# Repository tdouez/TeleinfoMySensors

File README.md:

# TeleinfoMySensors v2.1.0

Interface Téléinfo pour compteur Linky avec MySensors - version compatible mode standard et historique

Projet utilisant un Arduino Pro micro et un module NRF24L01

- Hardware disponible sur https://www.openhardware.io/view/744/MySensors-Linky
- Boîtier disponible sur https://www.thingiverse.com/thing:3985437
- Description disponible sur http://fumeebleue.fr

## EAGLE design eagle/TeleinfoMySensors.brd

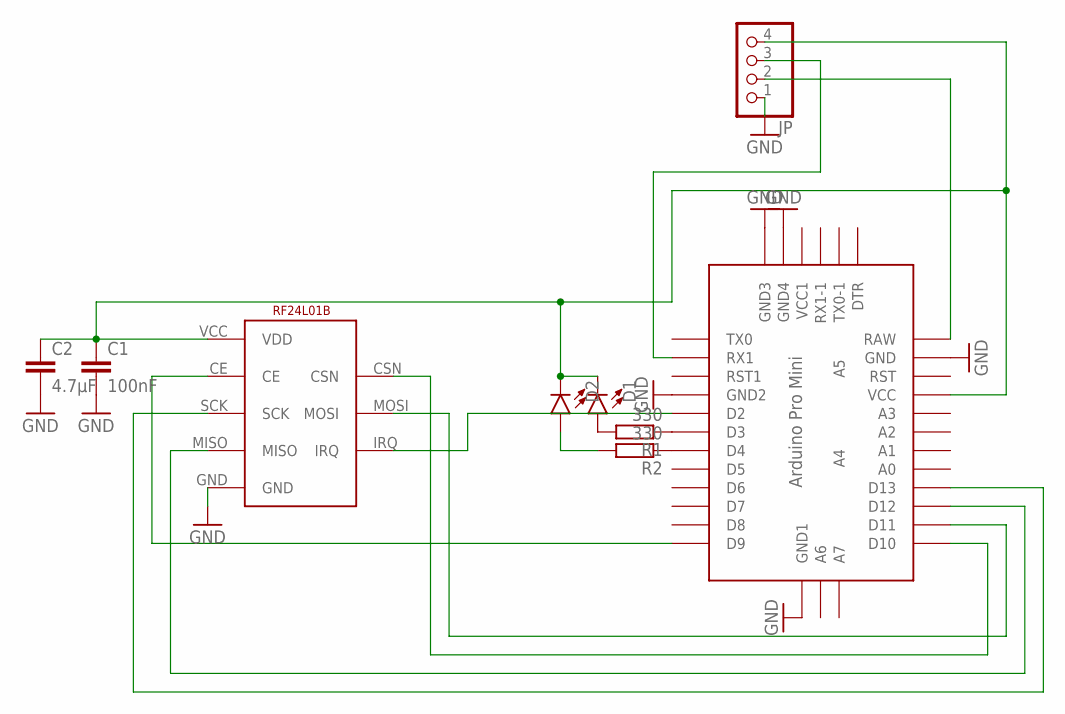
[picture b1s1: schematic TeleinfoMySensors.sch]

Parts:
C1: 100nF; C1206
C2: 4.7µF; C1210
D1, D2: LED1206; LED-1206
JP: PINHD-1X4; 1X04
NRF: NRF24L01BLACK; 24L01BLACK
R1, R2: 330; M1206
U$1: ABK-PRO-MINI

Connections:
GND: C1.2, C2.2, JP.1, NRF.GND, U$1.GND, U$1.GND1 (GND2), U$1.GND2 (GND3), U$1.GND3 (GND4), U$1.GND4 (GND1)
unnamed: NRF.CE, U$1.D9
unnamed: D1.A, R1.2
unnamed: NRF.SCK, U$1.D13
unnamed: R1.1, U$1.D3
unnamed: NRF.MOSI, U$1.D11
unnamed: NRF.MISO, U$1.D12
unnamed: JP.2, U$1.RAW
unnamed: R2.1, U$1.D4
unnamed: D2.A, R2.2
unnamed: JP.3, U$1.RX1
unnamed: C1.1, C2.1, D1.C, D2.C, JP.4, NRF.VCC (VDD), U$1.VCC
unnamed: NRF.IRQ, U$1.D2
unnamed: NRF.CSN, U$1.D10

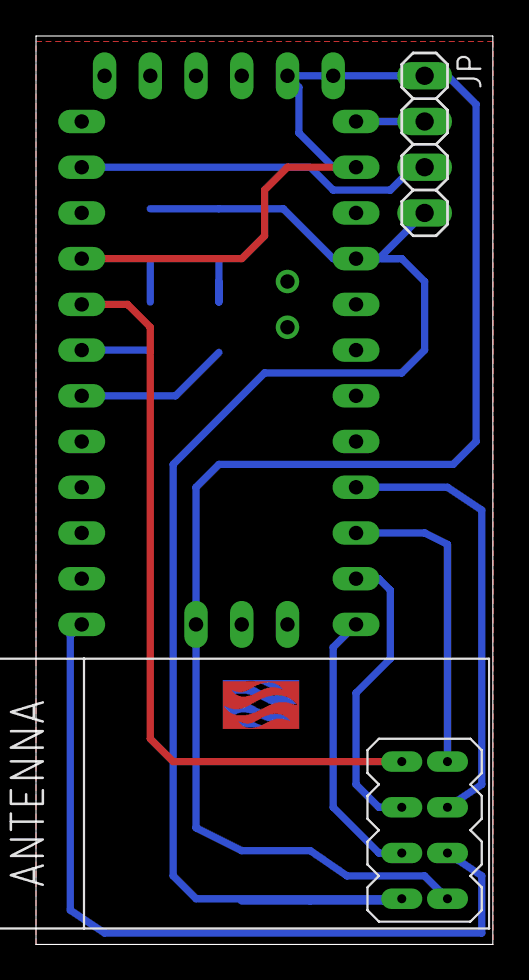
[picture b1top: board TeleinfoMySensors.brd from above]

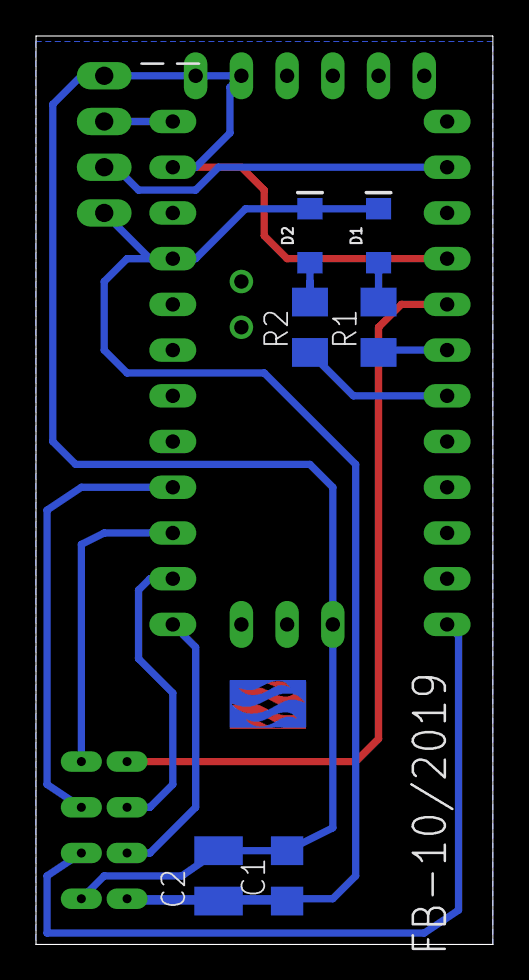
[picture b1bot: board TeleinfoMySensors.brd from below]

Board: 2 copper layers, 25.4 x 50.5 mm, 11 parts (7 on the bottom side), 14 nets.

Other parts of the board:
U$3, U$4: FB

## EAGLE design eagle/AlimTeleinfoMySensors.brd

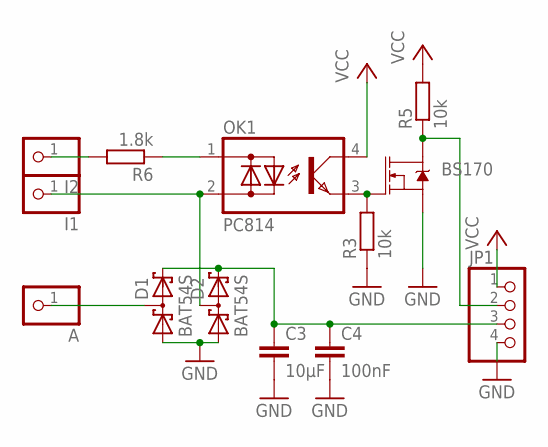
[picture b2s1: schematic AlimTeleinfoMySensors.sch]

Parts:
A: PINHD-1X1; 1X01
BS170: MOSFET-NCH-BSS138; SOT23-3
C3: 10µF; C1210
C4: 100nF; C1206
D1, D2: BAT54S; SOT23
I1, I2: PINHD-1X1; 1X01
JP1: PINHD-1X4; 1X04
OK1: PC814; DIL04
R3, R5: 10k; M1206
R6: 1.8k; M1206

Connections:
GND: BS170.2 (S), C3.2, C4.2, D1.1 (A1), D2.1 (A1), JP1.4, R3.1
unnamed: I2.1, R6.2
unnamed: D2.3 (C1A2), I1.1, OK1.2 (AC2)
unnamed: BS170.3 (D), JP1.2, R5.1
unnamed: C3.1, C4.1, D1.2 (C2), D2.2 (C2), JP1.3
unnamed: OK1.1 (AC1), R6.1
unnamed: BS170.1 (G), OK1.3 (E), R3.2
unnamed: A.1, D1.3 (C1A2)
VCC: JP1.1, OK1.4 (C), R5.2

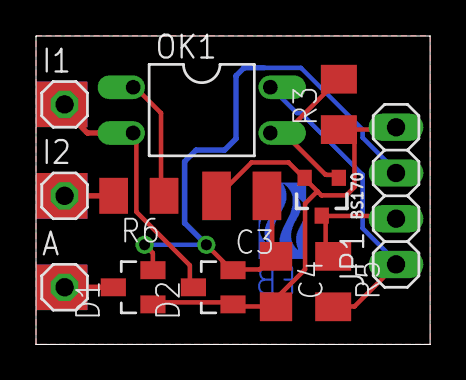
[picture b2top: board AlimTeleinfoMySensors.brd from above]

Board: 2 copper layers, 21.9 x 17.1 mm, 14 parts (0 on the bottom side), 9 nets.

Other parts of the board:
U$1: FB

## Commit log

2019-12-16 Create eagle
2019-12-16 Create t
2020-04-23 Add files via upload
    ADCO bug fix
2020-04-25 ADCO bug fix
    ADCO bug fix
2020-04-25 V1.1.0 compatible mode standard
2020-04-26 info data
2020-04-26 dev 26
2020-04-28 V1.1.0
    Version mode standard Linky
2020-08-21 V1.1.1
    V1.1.1
2020-08-26 V1.1.2
    - Ajout delais sur presentation et send, afin de soulager la gateway
    - Envoi données producteur et triphasé si besoin
    - Correction sur send EASF et EADS en WH au lieu du VA
2020-09-01 1.1.2
    - Ajout delais sur presentation et send, afin de soulager la gateway
    - Envoi données producteur et triphasé si besoin
    - Correction sur send EASF et EADS en WH au lieu du VA
    - Accents retirés sur les libellés de présentation
2020-10-23 options reglages NRF24L01
    Ajout options reglages NRF24L01 (puissance, débit, canal)
2020-10-26 1.1.4
    Optimisation bug fix
2021-05-12 1.1.5
    Correction erreur de compil et optimisation
2021-09-09 Fix display on entites on home assistant cf: https://www.home-assistant.io/integrations/sensor.mysensors/
2021-09-23 Create LICENSE
2021-09-24 Add node REPEATER
2021-09-26 Fix unit Wh from kwh send to controller
2021-10-05 Ajout prefixes et corrections sur type de compteur
    Ajout prefixes et corrections sur type de compteur
2022-06-24 V2.0.0
    Utilisation librairie universelle LibTeleinfo modifiée (pas d'enregistrement, pas assez de RAM sur l'ATmega328 pour avoir une solution stable en TIC full)
    Compatible mode historique et mode standard; détermination automatique au démarrage
    Attention tous les commandes MySensors ont été revues (n° différent pour certaines)
2022-09-27 v2.0.1
    Correction sur détection TIC standard
2022-12-20 2.0.3
    Kicad PCB with DIP switch
2023-01-27 v2.0.2
    Correction sur l'envoi des prefixes des chil_id_smax. Merci à Laurent B.
2023-02-02 V2.0.3
    Mise à jour librairie LibTeleinfo v1.1.5 avec derniers correctifs https://github.com/hallard/LibTeleinfo/releases
2023-02-27 v2.0.4
    Correction sur l'envoi des préfixes CHILD_ID_CCA*
2023-03-06 V2.0.5
    Optimisation mémoire
2023-04-17 v2.0.6
    Ajout temps maj pour éviter le spam de la gateway et contrôle étiquette BASE
2023-05-04 v2.0.7
    Amélioration détection mod eTIC historique/standard
2023-06-03 V2.0.8
    Correction detection TIC historique
2023-06-14 v2.0.9
    Ajout compatibilité Arduino pro micro et correction detection TIC historique
2023-06-15 v2.1.0
    Modification mise à jour gateway, plus de spam ni de perte d'étiquette.
    Code optimisé pour l'arduino pro micro ATMEGA32u4

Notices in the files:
parts and their libraries:
SparkFun-DiscreteSemi: Licensing: Creative Commons ShareAlike 4.0 International - https://creativecommons.org/licenses/by-sa/4.0
